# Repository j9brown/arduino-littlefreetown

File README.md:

# arduino-littlefreetown

Lighting controller for a two story combination Little Free Museum
and Little Free Library structure.

## Parts

PJRC Teensy 3.2 microcontroller
- https://www.pjrc.com/store/teensy32.html

FYSETC v2.1 LCD panel
- https://wiki.fysetc.com/Mini12864_Panel/
- https://github.com/FYSETC/FYSETC-Mini-12864-Panel
- https://www.amazon.com/FYSETC-Controller-Supports-Accessories-RGB-Backlight/dp/B08R9ZH7S2/

Adafruit bq24074 solar charger
- https://www.adafruit.com/product/4755

Adafruit 6 Volt 2 Watt solar panel

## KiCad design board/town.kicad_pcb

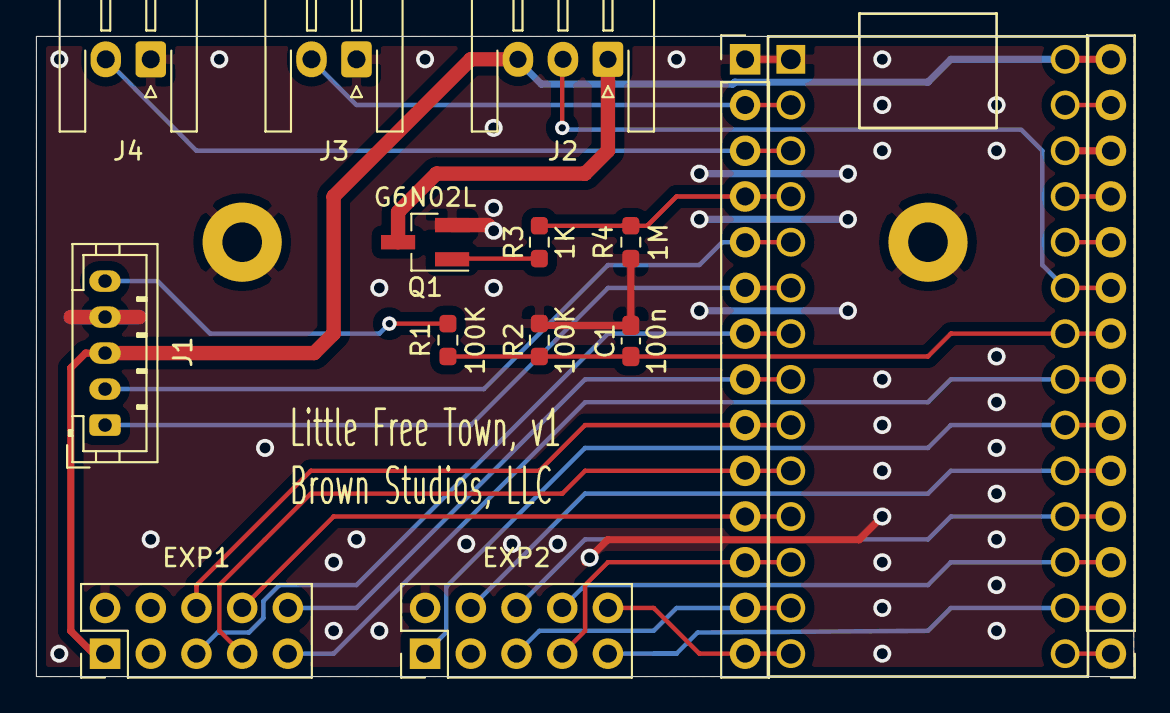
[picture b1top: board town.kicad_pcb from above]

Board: 2 copper layers, 61.0 x 35.6 mm, 17 parts (0 on the bottom side), 31 nets.

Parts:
C1: 100n; C_0603_1608Metric_Pad1.08x0.95mm_HandSolder
EXP1, EXP2: Panel Connector; PinHeader_2x05_P2.54mm_Vertical
H1, H2: Header; PinHeader_1x14_P2.54mm_Vertical
J1: Charger Connector; JST_PH_B5B-PH-K_1x05_P2.00mm_Vertical
J2: LED Strip Connector; JST_XH_S3B-XH-A-1_1x03_P2.50mm_Horizontal
J3, J4: Door Sensor; JST_XH_S2B-XH-A-1_1x02_P2.50mm_Horizontal
M1, M2: MountingHole_2.2mm_M2_Pad
Q1: G6N02L; SOT-23_Handsoldering
R1, R2: 100K; R_0603_1608Metric_Pad0.98x0.95mm_HandSolder
R3: 1K; R_0603_1608Metric_Pad0.98x0.95mm_HandSolder
R4: 1M; R_0603_1608Metric_Pad0.98x0.95mm_HandSolder
U1: Teensy3.2; Teensy32_HeadersOnly

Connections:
/AGND: H2.13, U1.32
/BATTMON: C1.1, H2.8, R1.2, R2.1, U1.27
/BEEP: EXP1.10, H1.8, U1.8
/BTN_EN1: EXP2.8, H2.3, U1.22
/BTN_EN2: EXP2.6, H2.4, U1.23
/BTN_ENC: EXP1.9, H2.7, U1.26
/CHG: H1.5, J1.2, U1.5
/DOOR1: H1.2, J3.2, U1.2
/DOOR2: H1.3, J4.2, U1.3
/LCD_A0: EXP1.7, H1.10, U1.10
/LCD_CS: EXP1.8, H1.11, U1.11
/LCD_RST: EXP1.6, H1.9, U1.9
/MISO: EXP2.10, H1.14, U1.14
/MOSI: EXP2.5, H1.13, U1.13
/PANEL_LED_DIN: EXP1.5, H1.7, U1.7
/PGOOD: H1.6, J1.1, U1.6
/SCK: EXP2.9, H2.2, U1.21
/SDCARD_CD: EXP2.4, H2.5, U1.24
/SDCARD_CS: EXP2.7, H1.12, U1.12
/STRIP_LED_DIN: H2.9, J2.2, U1.28
/STRIP_LED_EN: H1.4, R3.2, R4.1, U1.4
/STRIP_LED_GND: J2.1, Q1.3
/SW_KILL: EXP2.1, H2.6, U1.25
/VCC: H2.12, U1.31
/VLIPO: J1.5, R1.1
/X_A8: H2.10, U1.29
/X_A9: H2.11, U1.30
/X_D13: H2.1, U1.20
GND: C1.2, EXP1.2, EXP2.2, H1.1, J1.4, J3.1, J4.1, M1.1, M2.1, Q1.2, R2.2, R4.2, U1.1
unnamed: Q1.1, R3.1
VBUS: EXP1.1, H2.14, J1.3, J2.3, U1.33

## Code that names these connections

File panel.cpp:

#include <SPI.h>

#include "panel.h"
#include "utils.h"

namespace {
const u8g2_cb_t* LCD_ROTATION = U8G2_R2;
const int LCD_CS = 15;
const int LCD_A0 = 6;
const int LCD_RST = 5;
const int LCD_MOSI = 7;
const int LCD_SCK = 14;

const int LED_DIN = 4;

const int SW_KILL = 2;

const int BEEP = 9;

const int BTN_ENC = 8;
const int BTN_EN1 = 16;
const int BTN_EN2 = 17;
} // namespace

Panel* Panel::_self;

Panel::Panel() :
    _display(LCD_ROTATION, LCD_CS, LCD_A0, LCD_RST),
    _leds(3, LED_DIN, NEO_RGB | NEO_KHZ800),
    _knobEncoder(BTN_EN2, BTN_EN1),
    _knobRotations(0),
    _knobButton(BTN_ENC, INPUT_PULLUP),
    _killButton(SW_KILL, INPUT) {
}

void Panel::begin() {
  assert(_self == nullptr);
  _self = this;

  // Reassign the SPI pins
  SPI.setMOSI(LCD_MOSI);
  SPI.setSCK(LCD_SCK);

  // Initialize the display
  _display.begin();

  // Initialize the LEDs
  _leds.begin();
  _leds.show();

  // Initialize the rotary encoder
  _knobEncoder.begin();
  attachInterrupt(digitalPinToInterrupt(BTN_EN1), handleKnobRotation, CHANGE);
  attachInterrupt(digitalPinToInterrupt(BTN_EN2), handleKnobRotation, CHANGE);
}

void Panel::update() {
  // TODO: move to an ISR
  updateButton(&_knobButton, &_knobButtonEvent);
  updateButton(&_killButton, &_killButtonEvent);
}

void Panel::setColors(RGB display, RGB knob) {
  _leds.setPixelColor(0, display.r, display.g, display.b);
  _leds.setPixelColor(1, knob.r, knob.g, knob.b);
  _leds.setPixelColor(2, knob.r, knob.g, knob.b);
  _leds.show();
}

int32_t Panel::readKnobRotations() {
  int32_t count = _knobRotations;
  _knobRotations -= count;
  return count;
}

void Panel::handleKnobRotation() {
  switch (_self->_knobEncoder.read()) {
    case DIR_CW:
      _self->_knobRotations++;
      break;
    case DIR_CCW:
      _self->_knobRotations--;
      break;
  }
}

Panel::ButtonEvent Panel::readKnobButton() {
  ButtonEvent event = _knobButtonEvent;
  _knobButtonEvent = ButtonEvent::NONE;
  return event;
}

Panel::ButtonEvent Panel::readKillButton() {
  ButtonEvent event = _killButtonEvent;
  _killButtonEvent = ButtonEvent::NONE;
  return event;
}

void Panel::updateButton(Switch* button, volatile ButtonEvent* event) {
  button->poll();
  if (button->doubleClick()) {
    *event = ButtonEvent::DOUBLE_CLICK;
  } else if (button->singleClick()) {
    *event = ButtonEvent::SINGLE_CLICK;
  } else if (button->longPress()) {
    *event = ButtonEvent::LONG_PRESS;
  }
}

void Panel::playTone(uint32_t freq, uint32_t millis) {
  tone(BEEP, freq, millis);
}

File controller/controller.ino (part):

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 *
 * Wiring:
 * - see panel.h
 * - pin 0: DOOR1
 * - pin 1: DOOR2
 * - pin 2: STRIP_LED_EN
 * - pin 3: CHG
 * - pin 4: PGOOD
 * - pin 20/A6: BATTMON
 *           100 K resistor to Vbat
 *           100 K resistor to GND
 *           100 nF capacitor to GND
 * - pin 21: STRIP_LED_DIN
 * - cut trace between Vin and USB if using battery
 */

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  [] { return activityTimeoutSeconds.get() * 1000UL; });

constexpr int VBAT_PIN = A6;
constexpr int CHG_PIN = 3;
constexpr int PGOOD_PIN = 4;

Battery battery(VBAT_PIN);
BatteryHistory batteryHistory(&battery, batteryHistoryStorage);
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  }

  State newState = State::DISCHARGING;
  if (!digitalRead(CHG_PIN)) {
    newState = State::CHARGING;
  } else if (!digitalRead(PGOOD_PIN)) {
    newState = State::POWERED;
  }
  if (newState != _state) {
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  setLightsEnabled(false);

  // Initialize battery monitor
  pinMode(CHG_PIN, INPUT);
  pinMode(PGOOD_PIN, INPUT);

  // Setup sleeping
  // Periodically wake to update battery stats
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
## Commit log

2021-07-04 Initial commit of the display and UI framework.
2021-07-04 Add user activity timeouts.
2021-07-04 Add menu system and time picker.
2021-07-08 Added LED strip, more settings, color calculations.
2021-08-04 Add battery monitoring, strand test, and lights off features.
2021-08-05 Add a low battery cutoff.
2021-08-07 Rearrange files to make room for PCB design.
2021-08-31 Add PCB design.
2021-09-01 Update for new PCB design.
2021-09-01 Add low-power sleep mode.
2021-09-01 Only go to sleep when not animating lights.
2021-09-17 Add CAD export.
2021-09-17 Add support for showing charging state.
2021-09-17 Move battery monitor to main menu.
2021-09-17 Add door sensor support.
2021-09-19 Improve battery monitoring.
    Moved to new file.
    Clear stale data points after the device has been turned off
    for a while.
2021-10-15 Provide more control over lighting paramters.
    Also rotate the screen to allow for a vertical installation.
